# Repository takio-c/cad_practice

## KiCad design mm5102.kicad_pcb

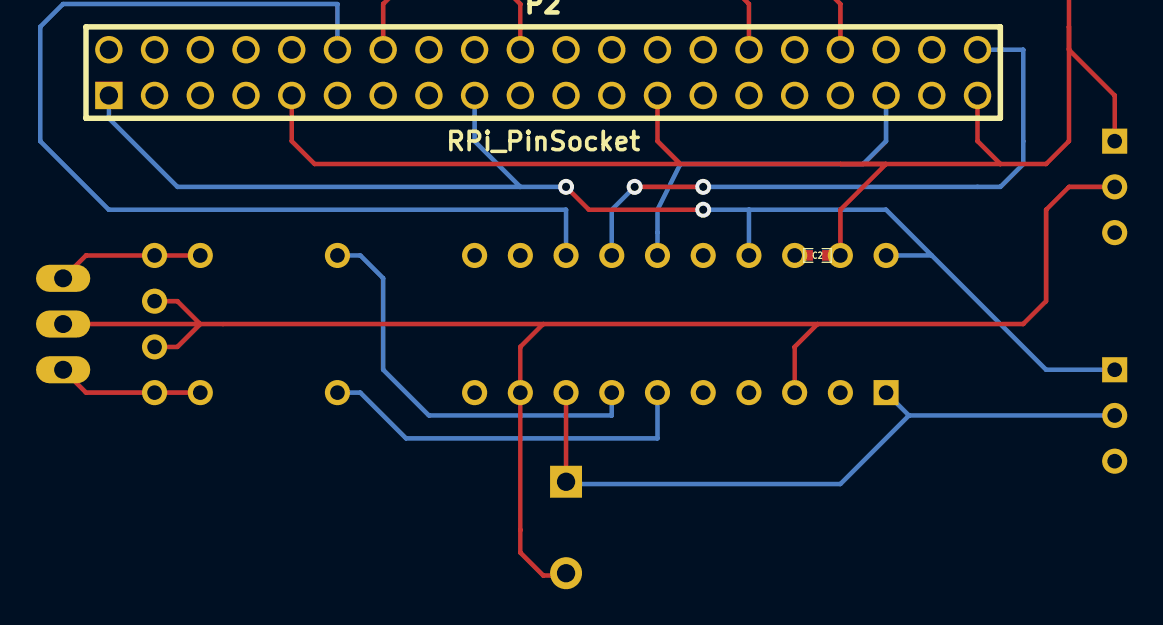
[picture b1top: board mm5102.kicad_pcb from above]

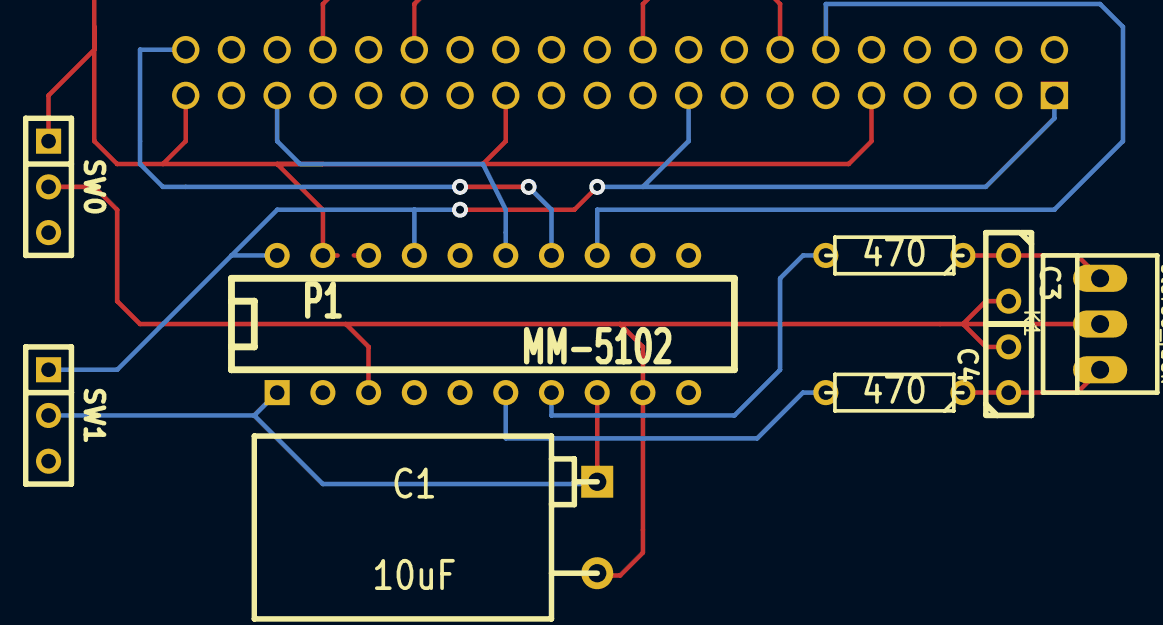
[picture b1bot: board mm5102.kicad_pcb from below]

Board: 2 copper layers, 11 parts (9 on the bottom side), 12 nets.

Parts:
C1: 10uF; CPR10X16
C2: 0.1uF; SM0402
C3, C4: 2200pF; C1
K1: stereo_jack; PINHEAD1-3
P1: MM-5102; DIP-20__300
P2: RPi_PinSocket; PIN_ARRAY_20X2
R1, R2: 470; R3
SW0: SEL_AGND; MICROSWITCH_SPST
SW1: SEL_A33V; MICROSWITCH_SPST

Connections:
unnamed: P1.6, R1.2
unnamed: P1.7, R2.2
unnamed: P1.14, P2.40
unnamed: P1.15, P2.35
unnamed: P1.13, P2.12
unnamed: C2.1, P1.18
unnamed: C3.1, K1.3, R2.1
unnamed: C4.1, K1.1, R1.1
analog_3.3v: C1.1, P1.1, P1.8, SW1.2
analog_gnd: C1.2, C3.2, C4.2, K1.2, P1.3, P1.9, SW0.2
digital_3.3v: P1.17, P1.20, P2.1, P2.17, SW1.1
digital_gnd: C2.2, P1.19, P2.9, P2.14, P2.20, P2.25, P2.30, P2.34, P2.39, SW0.1

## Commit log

2016-05-26 draft
